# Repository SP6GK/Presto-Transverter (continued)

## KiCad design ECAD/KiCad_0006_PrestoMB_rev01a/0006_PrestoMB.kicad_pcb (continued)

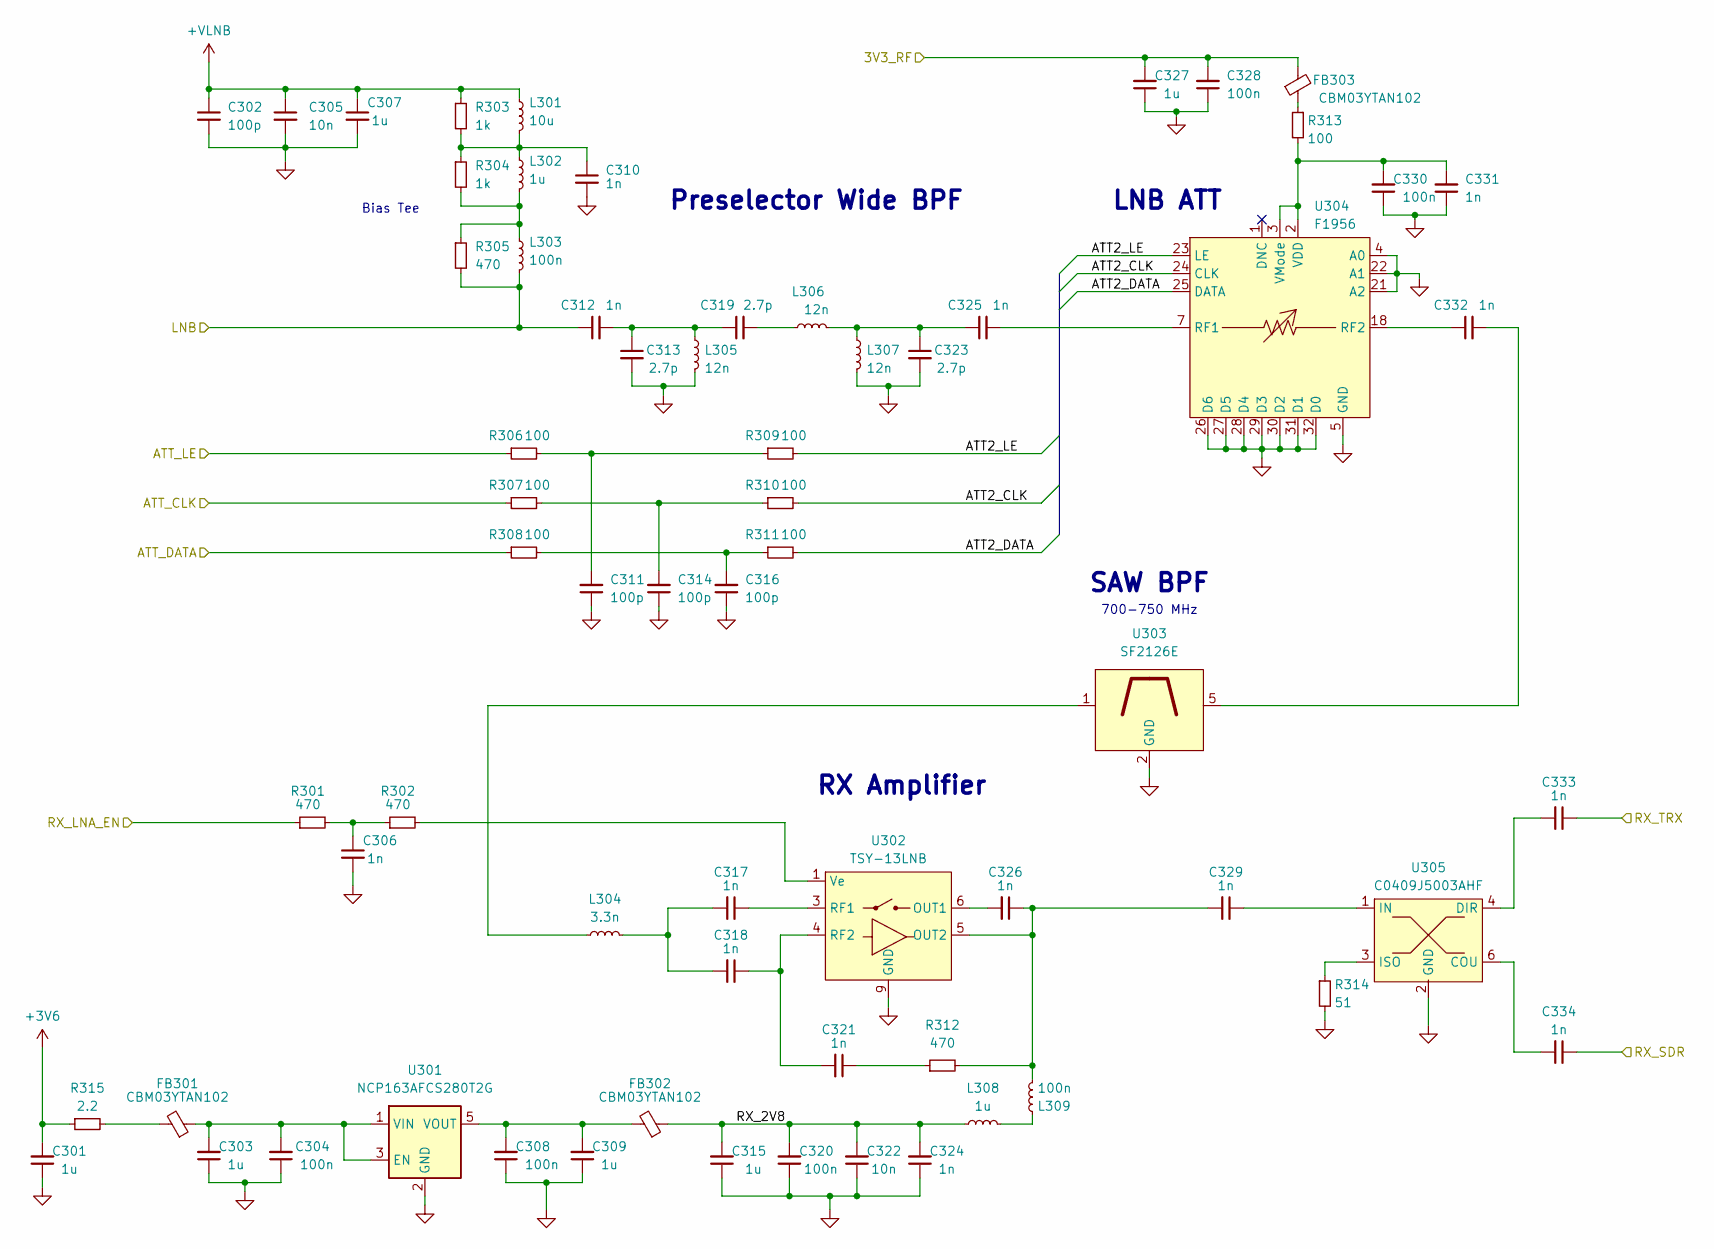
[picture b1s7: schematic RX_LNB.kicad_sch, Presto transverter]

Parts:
C301, C303, C309, C315, C327: 1u; C_0603_1608Metric_Pad1.08x0.95mm_HandSolder
C302: 100p; C_0805_2012Metric_Pad1.18x1.45mm_HandSolder
C304, C308, C320, C328: 100n; C_0603_1608Metric_Pad1.08x0.95mm_HandSolder
C305: 10n; C_0805_2012Metric_Pad1.18x1.45mm_HandSolder
C306: 1n; C_0603_1608Metric
C307: 1u; C_1206_3216Metric_Pad1.33x1.80mm_HandSolder
C310: 1n; C_1206_3216Metric_Pad1.33x1.80mm_HandSolder
C311, C314, C316: 100p; C_0603_1608Metric_Pad1.08x0.95mm_HandSolder
C312: 1n; C_0805_2012Metric
C313, C319, C323: 2.7p; C_0603_1608Metric
C317, C318, C321, C326, C329, C331, C333, C334: 1n; C_0402_1005Metric_Pad0.74x0.62mm_HandSolder
C322: 10n; C_0603_1608Metric_Pad1.08x0.95mm_HandSolder
C324, C325, C332: 1n; C_0603_1608Metric_Pad1.08x0.95mm_HandSolder
C330: 100n; C_0402_1005Metric_Pad0.74x0.62mm_HandSolder
FB301, FB302, FB303: CBM03YTAN102; L_0603_1608Metric_Pad1.05x0.95mm_HandSolder
L301: 10u; L_1210_3225Metric_Pad1.42x2.65mm_HandSolder
L302: 1u; L_0805_2012Metric_Pad1.15x1.40mm_HandSolder
L303: 100n; L_0603_1608Metric_Pad1.05x0.95mm_HandSolder
L304: 3.3n; L_0603_1608Metric_Pad1.05x0.95mm_HandSolder
L305, L306, L307: 12n; L_0603_1608Metric
L308: 1u; L_0805_2012Metric_Pad1.05x1.20mm_HandSolder
L309: 100n; L_0603_1608Metric
R301, R302: 470; R_0402_1005Metric_Pad0.72x0.64mm_HandSolder
R303, R304: 1k; R_0805_2012Metric_Pad1.20x1.40mm_HandSolder
R305: 470; R_0603_1608Metric_Pad0.98x0.95mm_HandSolder
R306, R307, R308, R309, R310, R311, R313: 100; R_0402_1005Metric_Pad0.72x0.64mm_HandSolder
R312: 470; C_0402_1005Metric_Pad0.74x0.62mm_HandSolder
R314: 51; R_0603_1608Metric_Pad0.98x0.95mm_HandSolder
R315: 2.2; R_0402_1005Metric_Pad0.72x0.64mm_HandSolder
U301: NCP163AFCS280T2G; SOT-23-5
U302: TSY-13LNB; MiniCircuits_MC163_TSY13LNB
U303: SF2126E; 3x3mm_RFMI_SF2126E
U304: F1956; TQFN-32-1EP_5x5mm_P0.5mm_EP3.1x3.1mm
U305: C0409J5003AHF

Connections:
3V6: C301.2, R315.1; also elsewhere on the board
3v3_RF: C327.2, C328.2, FB303.2; also elsewhere on the board
+VLNB: C302.1, C305.1, C307.1, L301.1, R303.1; also elsewhere on the board
/ATT_CLK: R307.1; also elsewhere on the board
/ATT_DATA: R308.1; also elsewhere on the board
/ATT_LE: R306.1; also elsewhere on the board
/Input_&_IF_Mixer/RX_TRX: C333.1; also elsewhere on the board
/RX_LNA_EN: R301.1; also elsewhere on the board
/RX_LNB/ATT2_CLK: R310.2, U304.24 (CLK)
/RX_LNB/ATT2_DATA: R311.2, U304.25 (DATA)
/RX_LNB/ATT2_LE: R309.2, U304.23 (LE)
/RX_LNB/LNB: C312.1, L303.2, R305.2; also elsewhere on the board
/RX_LNB/RX_2V8: C315.2, C320.2, C322.2, C324.2, FB302.1, L308.2
/RX_LNB/RX_SDR: C334.1; also elsewhere on the board
GND: C301.1, C302.2, C303.1, C304.1, C305.2, C306.2, C307.2, C308.1, C309.1, C310.2, C311.1, C313.2, C314.1, C315.1, C316.1, C320.1, C322.1, C323.2, C324.1, C327.1, C328.1, C330.1, C331.1, L305.2, L307.2, R314.2, U301.2 (GND), U302.2 (GND), U302.7 (GND), U302.8 (GND), U302.9 (GND), U303.2 (GND), U303.3 (GND), U303.4 (GND), U303.6 (GND), U303.7 (GND), U303.8 (GND), U304.4 (A0), U304.5 (GND), U304.6 (GND), U304.8 (GND), U304.9 (GND), U304.10 (GND), U304.11 (GND), U304.12 (GND), U304.13 (GND), U304.14 (GND), U304.15 (GND), U304.16 (GND), U304.17 (GND), U304.19 (GND), U304.20 (GND), U304.21 (A2), U304.22 (A1), U304.26 (D6), U304.27 (D5), U304.28 (D4), U304.29 (D3), U304.30 (D2), U304.31 (D1), U304.32 (D0), U304.33 (GND), U305.2 (GND), U305.5 (GND); also elsewhere on the board
unnamed: C306.1, R301.2, R302.1
unnamed: C310.1, L301.2, L302.1, R303.2, R304.1
unnamed: C311.2, R306.2, R309.1
unnamed: C312.2, C313.1, C319.1, L305.1
unnamed: C314.2, R307.2, R310.1
unnamed: C316.2, R308.2, R311.1
unnamed: C317.2, C318.2, L304.2
unnamed: C319.2, L306.1
unnamed: C321.1, R312.1
unnamed: C323.1, C325.1, L306.2, L307.1
unnamed: C332.2, U303.5
unnamed: FB301.2, R315.2
unnamed: FB303.1, R313.1
unnamed: L302.2, L303.1, R304.2, R305.1
unnamed: L304.1, U303.1
unnamed: L308.1, L309.2
unnamed: C303.2, C304.2, FB301.1, U301.1 (VIN), U301.3 (EN)
unnamed: C308.2, C309.2, FB302.2, U301.5 (VOUT)
unnamed: C326.2, U302.6 (OUT1)
unnamed: C326.1, C329.2, L309.1, R312.2, U302.5 (OUT2)
unnamed: C317.1, U302.3 (RF1)
unnamed: C318.1, C321.2, U302.4 (RF2)
unnamed: R302.2, U302.1 (Ve)
unnamed: C325.2, U304.7 (RF1)
unnamed: C332.1, U304.18 (RF2)
unnamed: C330.2, C331.2, R313.2, U304.2 (VDD), U304.3 (VMode)
unnamed: C334.2, U305.6 (COU)
unnamed: C333.2, U305.4 (DIR)
unnamed: C329.1, U305.1 (IN)
unnamed: R314.1, U305.3 (ISO)

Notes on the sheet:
LNB ATT
700-750 MHz
Preselector Wide BPF
RX Amplifier
Bias Tee
SAW BPF

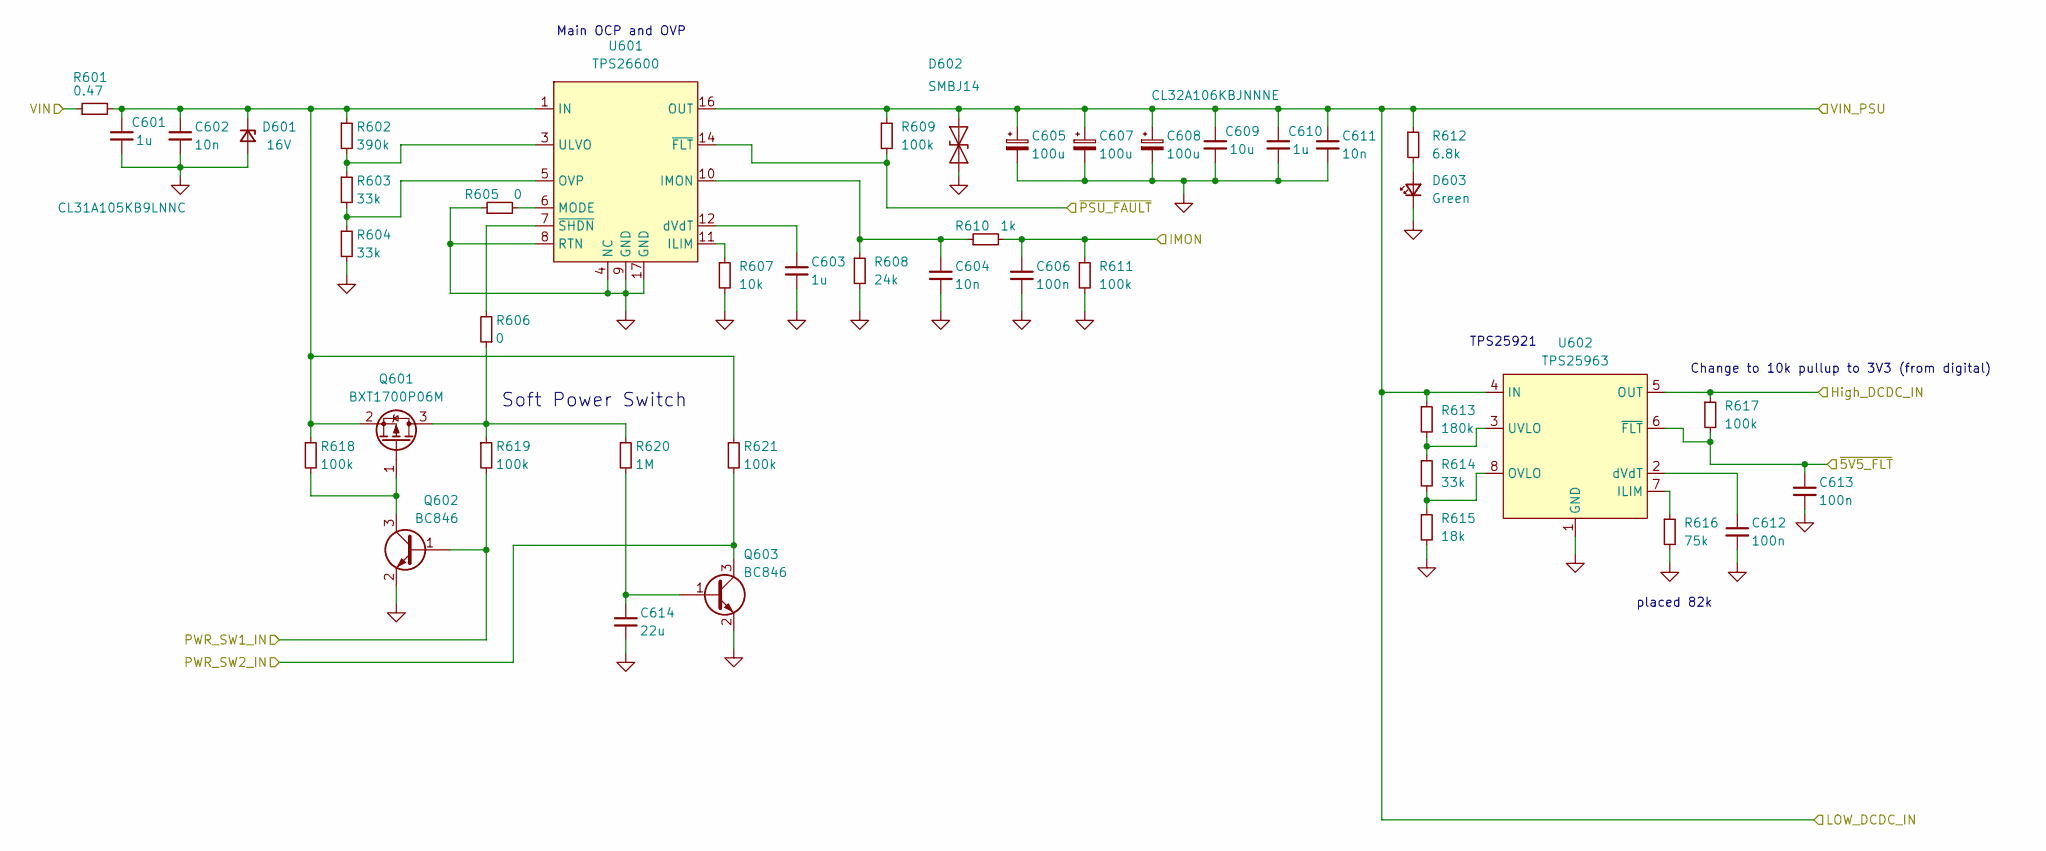
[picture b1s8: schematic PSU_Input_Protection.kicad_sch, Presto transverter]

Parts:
C601, C610: 1u; C_1206_3216Metric_Pad1.33x1.80mm_HandSolder
C602, C611: 10n; C_0805_2012Metric_Pad1.18x1.45mm_HandSolder
C603: 1u; C_0805_2012Metric_Pad1.18x1.45mm_HandSolder
C604: 10n; C_0402_1005Metric_Pad0.74x0.62mm_HandSolder
C605, C607, C608: 100u; CP_Elec_10x10.5
C606: 100n; C_0402_1005Metric_Pad0.74x0.62mm_HandSolder
C609: 10u; C_1210_3225Metric_Pad1.33x2.70mm_HandSolder
C612, C613: 100n; C_0805_2012Metric_Pad1.18x1.45mm_HandSolder
C614: 22u; C_0805_2012Metric_Pad1.18x1.45mm_HandSolder
D601: 16V; D_SMA
D602: SMBJ14; D_SMA
D603: Green; D_0805_2012Metric_Pad1.15x1.40mm_HandSolder
Q601: BXT1700P06M; SOT-23
Q602, Q603: BC846; SOT-23
R601: 0.47; R_1206_3216Metric_Pad1.30x1.75mm_HandSolder
R602: 390k; R_0805_2012Metric_Pad1.20x1.40mm_HandSolder
R603, R604, R614: 33k; R_0805_2012Metric_Pad1.20x1.40mm_HandSolder
R605, R606: 0; R_0603_1608Metric_Pad0.98x0.95mm_HandSolder
R607: 10k; R_0603_1608Metric_Pad0.98x0.95mm_HandSolder
R608: 24k; R_0603_1608Metric_Pad0.98x0.95mm_HandSolder
R609, R617: 100k; R_0603_1608Metric_Pad0.98x0.95mm_HandSolder
R610: 1k; R_0402_1005Metric_Pad0.72x0.64mm_HandSolder
R611: 100k; R_0402_1005Metric_Pad0.72x0.64mm_HandSolder
R612: 6.8k; R_0603_1608Metric_Pad0.98x0.95mm_HandSolder
R613: 180k; R_0805_2012Metric_Pad1.20x1.40mm_HandSolder
R615: 18k; R_0805_2012Metric_Pad1.20x1.40mm_HandSolder
R616: 75k; R_0603_1608Metric_Pad0.98x0.95mm_HandSolder
R618, R619, R621: 100k; R_0805_2012Metric_Pad1.20x1.40mm_HandSolder
R620: 1M; R_0805_2012Metric_Pad1.20x1.40mm_HandSolder
U601: TPS26600; HTSSOP-16-1EP_4.4x5mm_P0.65mm_EP3.4x5mm_Mask2.46x2.31mm
U602: TPS25963; SOIC-8-1EP_3.9x4.9mm_P1.27mm_EP2.62x3.51mm

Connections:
+VIN: C605.1, C607.1, C608.1, C609.1, C610.1, C611.1, D602.1 (A1), R609.1, R612.1, R613.1, U601.15 (OUT), U601.16 (OUT), U602.4 (IN); also elsewhere on the board
/PSU_LNB/PSU_Input_Protection/High_DCDC_IN: R617.1, U602.5 (OUT); also elsewhere on the board
/PSU_LNB/PSU_Input_Protection/IMON: C606.1, R610.2, R611.1; also elsewhere on the board
/PSU_LNB/PSU_Input_Protection/~5V5_FLT: C613.1, R617.2, U602.6 (~FLT); also elsewhere on the board
/PSU_LNB/PSU_Input_Protection/~PSU_FAULT: R609.2, U601.14 (~FLT); also elsewhere on the board
/PSU_LNB/PW_SW1: Q602.1 (B), R619.2; also elsewhere on the board
/PSU_LNB/PW_SW2: Q603.3 (C), R621.2; also elsewhere on the board
/PSU_LNB/VIN: R601.1; also elsewhere on the board
GND: C601.2, C602.2, C603.2, C604.2, C605.2, C606.2, C607.2, C608.2, C609.2, C610.2, C611.2, C612.2, C613.2, C614.2, D601.2 (A), D602.2 (A2), D603.1 (K), Q602.2 (E), Q603.2 (E), R604.2, R605.1, R607.2, R608.2, R611.2, R615.2, R616.2, U601.4 (NC), U601.8 (RTN), U601.9 (GND), U601.13 (NC), U601.17 (GND), U602.1 (GND), U602.9 (GND); also elsewhere on the board
unnamed: C601.1, C602.1, D601.1 (K), Q601.2, R601.2, R602.1, R618.1, R621.1, U601.1 (IN), U601.2 (IN)
unnamed: D603.2 (A), R612.2
unnamed: Q601.3, R606.1, R619.1, R620.1
unnamed: Q601.1, Q602.3 (C), R618.2
unnamed: C614.1, Q603.1 (B), R620.2
unnamed: R607.1, U601.11 (ILIM)
unnamed: C604.1, R608.1, R610.1, U601.10 (IMON)
unnamed: R605.2, U601.6 (MODE)
unnamed: R603.2, R604.1, U601.5 (OVP)
unnamed: R602.2, R603.1, U601.3 (ULVO)
unnamed: C603.1, U601.12 (dVdT)
unnamed: R606.2, U601.7 (~SHDN)
unnamed: R616.1, U602.7 (ILIM)
unnamed: R614.2, R615.1, U602.8 (OVLO)
unnamed: R613.2, R614.1, U602.3 (UVLO)
unnamed: C612.1, U602.2 (dVdT)

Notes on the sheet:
Change to 10k pullup to 3V3 (from digital)
Main OCP and OVP
TPS25921
placed 82k
Soft Power Switch

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
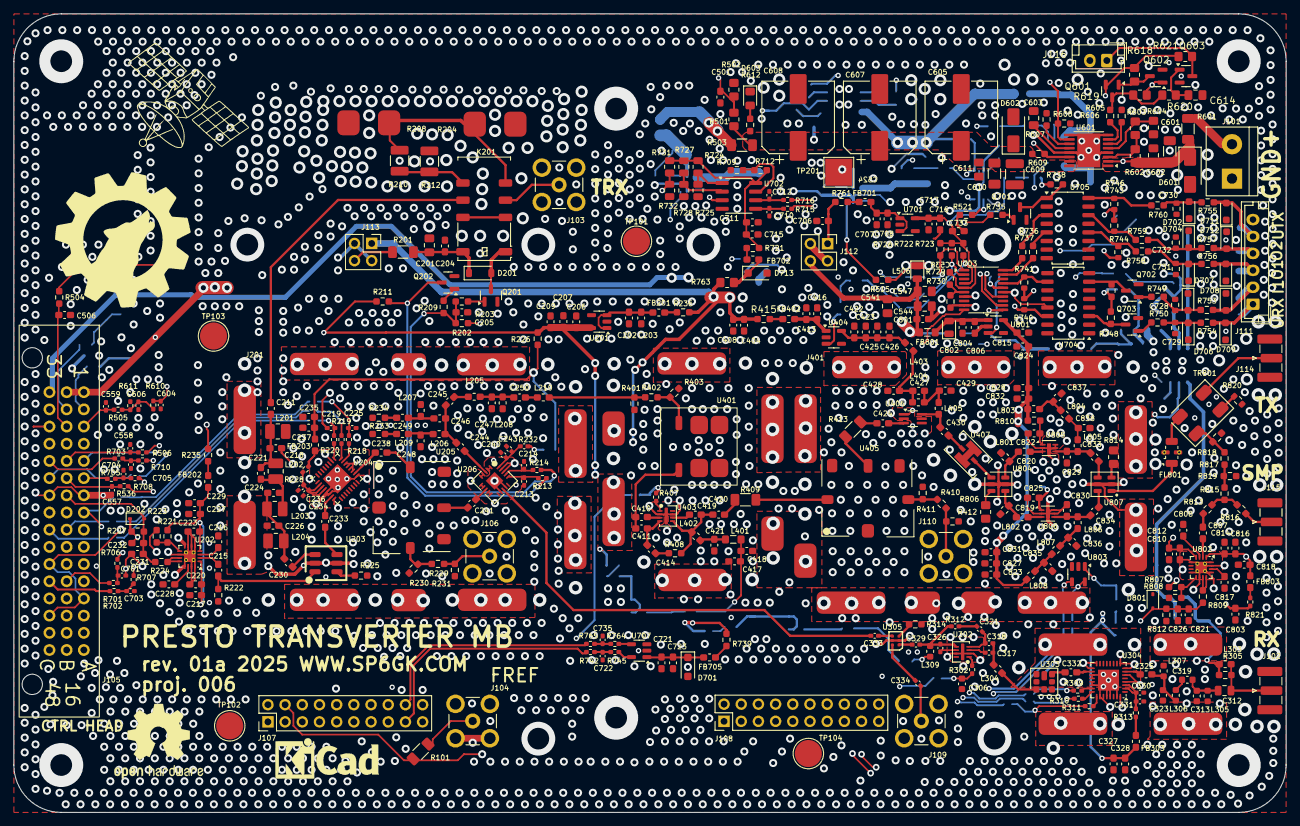
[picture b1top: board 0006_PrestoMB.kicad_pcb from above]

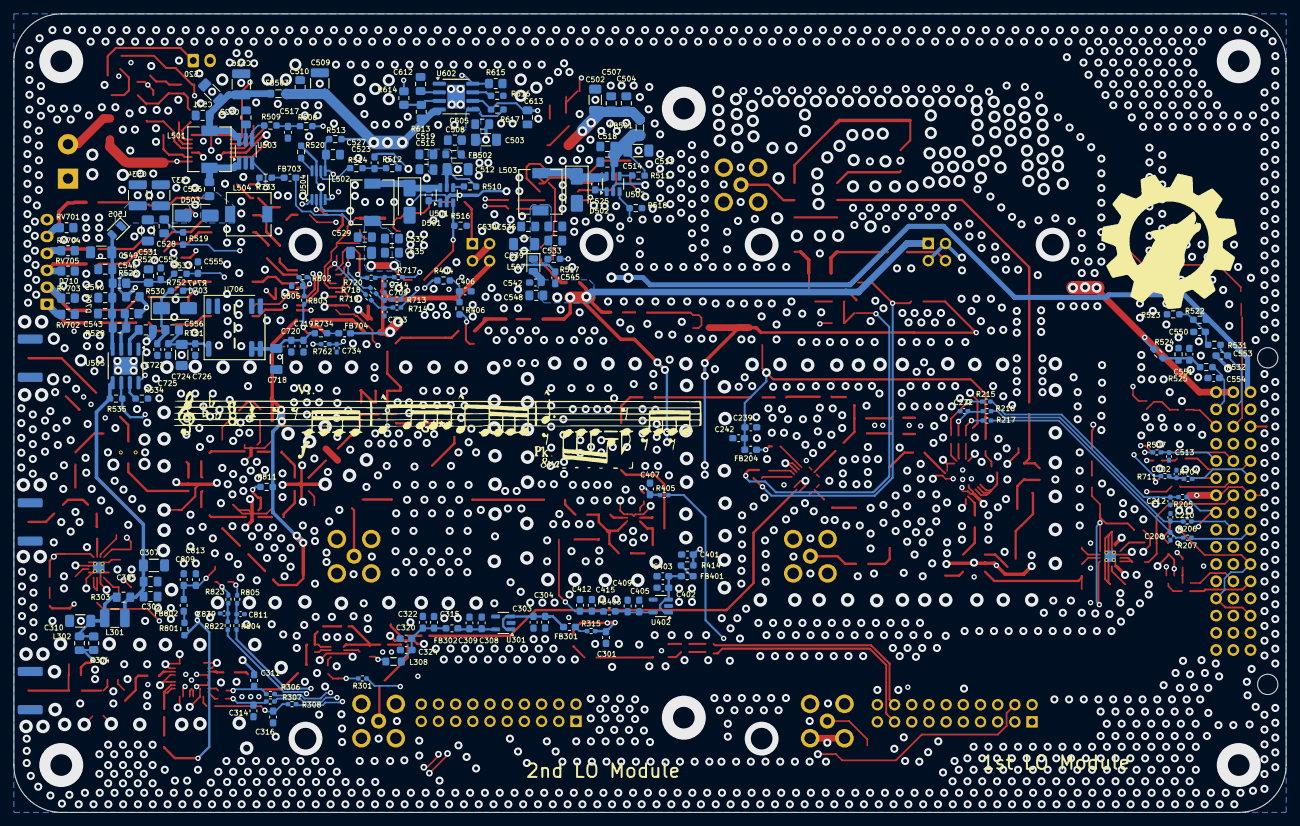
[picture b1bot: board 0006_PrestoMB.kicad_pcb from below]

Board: 4 copper layers, 188.0 x 118.0 mm, 666 parts (209 on the bottom side), 340 nets.

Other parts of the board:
J413#2, J413#3, J413#4, J413#5: TC-01; TC-01_CLIP_LeaderTech
J**: MS350-20S

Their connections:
GND: J413#2.1, J413#3.1, J413#4.1, J413#5.1; also elsewhere on the board
